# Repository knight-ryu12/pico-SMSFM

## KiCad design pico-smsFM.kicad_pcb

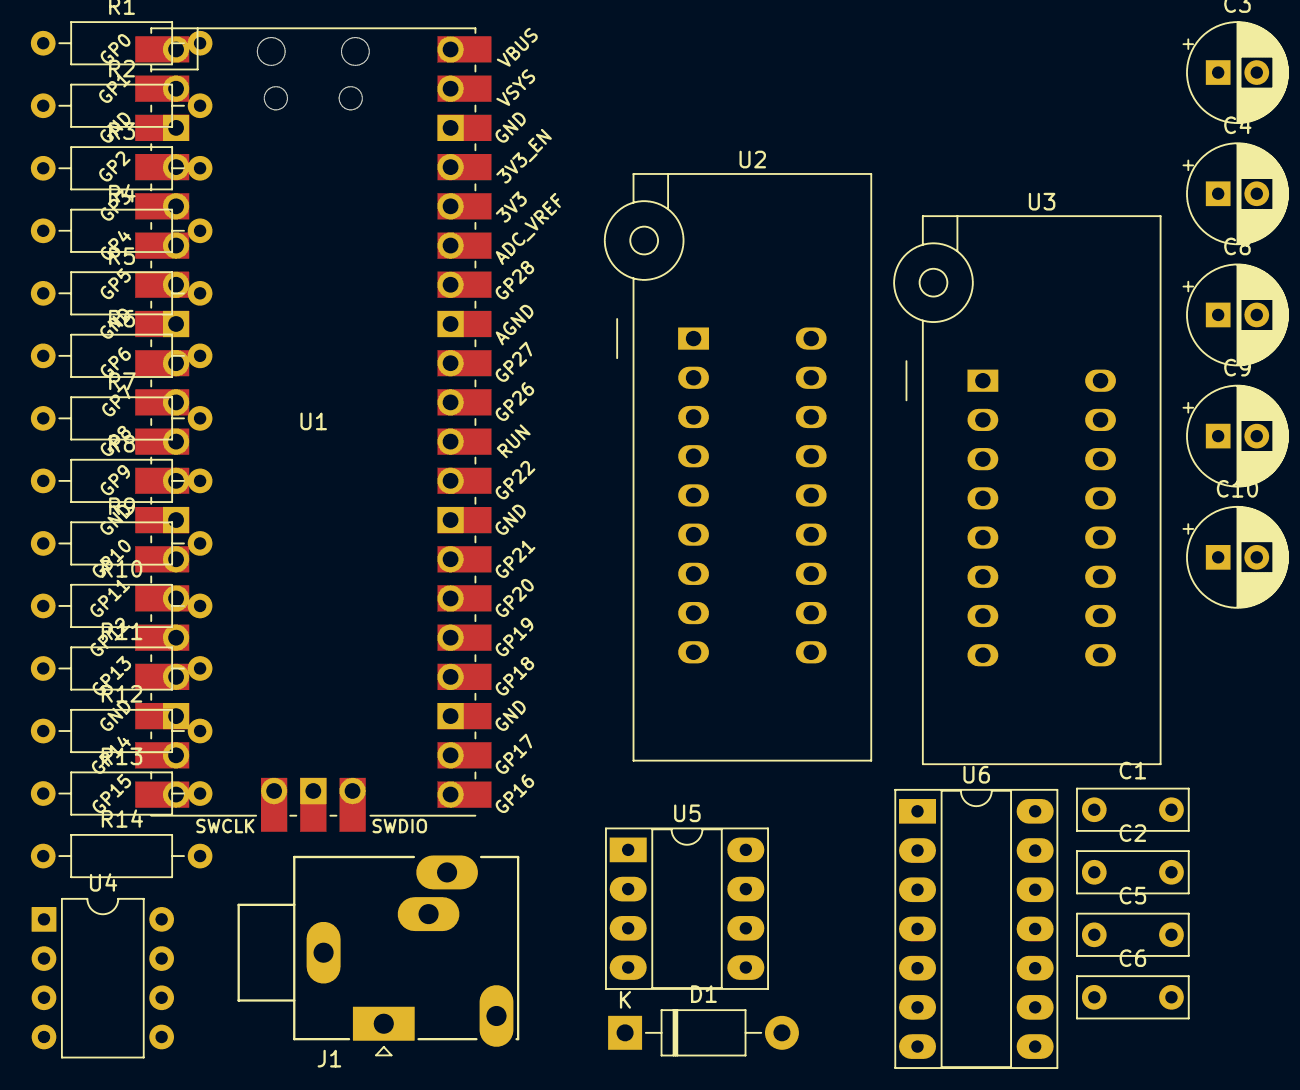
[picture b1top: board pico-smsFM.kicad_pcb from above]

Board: 2 copper layers, 31 parts (0 on the bottom side), 37 nets, no tracks yet.

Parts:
C1, C2: 0.015u/15n; C_Disc_D7.0mm_W2.5mm_P5.00mm
C3, C8, C9, C10: C; CP_Radial_D6.3mm_P2.50mm
C4: 10u; CP_Radial_D6.3mm_P2.50mm
C5: 4.7u; C_Disc_D7.0mm_W2.5mm_P5.00mm
C6: 820p; C_Disc_D7.0mm_W2.5mm_P5.00mm
D1: D; D_DO-41_SOD81_P10.16mm_Horizontal
J1: AudioJack3_SwitchTR; Jack_3.5mm_Ledino_KB3SPRS_Horizontal
R1, R2, R5, R6, R7, R8, R9, R10, R12, R13: 4.7k; R_Axial_DIN0207_L6.3mm_D2.5mm_P10.16mm_Horizontal
R3, R4, R11: 2.2k; R_Axial_DIN0207_L6.3mm_D2.5mm_P10.16mm_Horizontal
R14: 10k; R_Axial_DIN0207_L6.3mm_D2.5mm_P10.16mm_Horizontal
U1: Pico; RPi_Pico_SMD_TH
U2: YM2413; DIP_Socket-18_W4.3_W5.08_W7.62_W10.16_W10.9_3M_218-3341-00-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
U3: SN76489; DIP_Socket-16_W4.3_W5.08_W7.62_W10.16_W10.9_3M_216-3340-00-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
U4: AE-Si5351A; DIP-8_W7.62mm
U5: NJM4580; DIP-8_W7.62mm_Socket_LongPads
U6: 4066; DIP-14_W7.62mm_Socket_LongPads

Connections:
+3V3: R12.2, R13.2, U1.36 (3V3), U4.1 (VDDO), U4.8 (VDD)
+5V: C3.1, C8.1, C9.2, C10.2, D1.1 (K), R8.1, U2.16 (VCC), U3.16 (VCC), U5.8 (V+), U6.14 (VDD)
/D0: U1.1 (GPIO0), U2.17 (D0), U3.3 (D0)
/D1: U1.2 (GPIO1), U2.18 (D1), U3.2 (D1)
/D2: U1.4 (GPIO2), U2.2 (D2), U3.1 (D2)
/D3: U1.5 (GPIO3), U2.3 (D3), U3.15 (D3)
/D4: U1.6 (GPIO4), U2.4 (D4), U3.13 (D4)
/D5: U1.7 (GPIO5), U2.5 (D5), U3.12 (D5)
/D6: U1.9 (GPIO6), U2.6 (D6), U3.11 (D6)
/D7: U1.10 (GPIO7), U2.7 (D7), U3.10 (D7)
A0: U1.17 (GPIO13), U2.10 (A0)
CLK0: U2.8 (XIN), U4.5 (CLK0)
CLK1: U3.14 (CLOCK), U4.6 (CLK1)
GND: C1.2, C2.2, C3.2, C4.2, C8.2, C9.1, C10.1, J1.S, R3.1, R4.1, R9.2, U1.3 (GND), U1.8 (GND), U1.13 (GND), U1.18 (GND), U1.23 (GND), U1.28 (GND), U1.33 (AGND), U1.38 (GND), U2.1 (GND), U3.8 (GND), U4.4 (GND), U5.4 (V-), U6.7 (VSS)
I2C_SCL: R12.1, U1.22 (GPIO17), U4.2 (SCL)
I2C_SDA: R13.1, U1.21 (GPIO16), U4.3 (SDA)
LPF_BYPASS: U1.26 (GPIO20), U6.13
MUSIC_OUT: R2.1, R3.2, U2.14 (MO)
unnamed: C1.1, R1.2, R6.1
unnamed: C2.1, R2.2, R5.1
unnamed: C5.1, R14.2, U5.7, U6.2
unnamed: C5.2, R11.1
unnamed: C6.2, U6.1
unnamed: R5.2, R6.2, U6.3
unnamed: J1.R, J1.T, R11.2
unnamed: R7.2, U6.4
unnamed: R10.1, U5.2 (-)
unnamed: C6.1, R10.2, R14.1, U5.1, U5.6 (-)
RHYTHM_OUT: R1.1, R4.2, U2.15 (RO)
SN_MUTE: U1.25 (GPIO19), U6.5
SN_OUT: R7.1, U3.7 (AUDIO_OUT)
VDD1/2_BIAS: C4.1, D1.2 (A), R8.2, R9.1, U1.31 (GPIO26_ADC0), U5.3 (+), U5.5 (+)
~SN_CS: U1.15 (GPIO11), U3.6 (~CE)
~SN_WR: U1.16 (GPIO12), U3.5 (~WE)
~YM_CS: U1.12 (GPIO9), U2.12 (~CS)
~YM_RESET: U1.11 (GPIO8), U2.13 (~IC)
~YM_WR: U1.14 (GPIO10), U2.11 (~WE)

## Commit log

2024-06-18 Add decoupling cap
    Add more logic wire
2024-07-01 Add more logics
